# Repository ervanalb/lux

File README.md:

lux
===

Lux is a protocol for the transmission of power and data from a host device to one or more nodes. It is capable of data rates approaching 3 megabits per second and supplying 30 Watts of power over distances of up to 100 feet. It is designed to be easy to implement and uses low-cost cabling and connectors.

Lux was designed as a lighting control protocol, specifically for LED strips. But, it generalizes nicely to any sort of automation on a small to medium scale.

For tech-specs of the protocol, see SPECS.md.

In this repository, you will find:

Library
-------

The lux library is a architecture-independent implementation of the lux in C which you can use to implement your own lux nodes. Simply provide the necessary simple hardware abstraction layer, and you're good to go. The implementation fits in under 8K of program memory and 2K of RAM (1K of which is shared with the application) on a Cortex-M0.

LED strip firmware
------------------

This is a real-world instantiation of the lux protocol to control WS2811 or LPD6803 light strips. It uses a STM32F030 at 48 MHz, which has only 32K of FLASH and 4K of RAM for all of the processing. The code also implements a bootloader for firmware upgrades over lux.

Python
------

There is also a python implementation of a lux master using pyserial.

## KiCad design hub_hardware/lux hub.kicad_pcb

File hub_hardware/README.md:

Lux Hub Hardware
================

History
-------

### Rev 6

#### Errata

- 

##### Bad parts

- U3
- R42
- C3 is short
- Fuse clips
- CON1 holes should be bigger

### Rev 5

- STM32F042
- 6 Lux outputs
    - 48V power, 5V/0V RS-422 data
    - Data lines tied together
    - Rx/Tx enable are indepedent
    - TVS on data lines
    - Per-output PTC fuses (which weren't useful)
- USB for comms & non-48V power
    - Spec'd for 500mA current draw to drive 6 ports
- *Greenwire*: 3v3 reg `U1` pads are incorrect
- *Greenwire*: Inrush limiter changed: `R42 -> C; C1 -> R; R1` unpopulated
- *Greenwire*: RX pin incorrect; shorted to TX LED

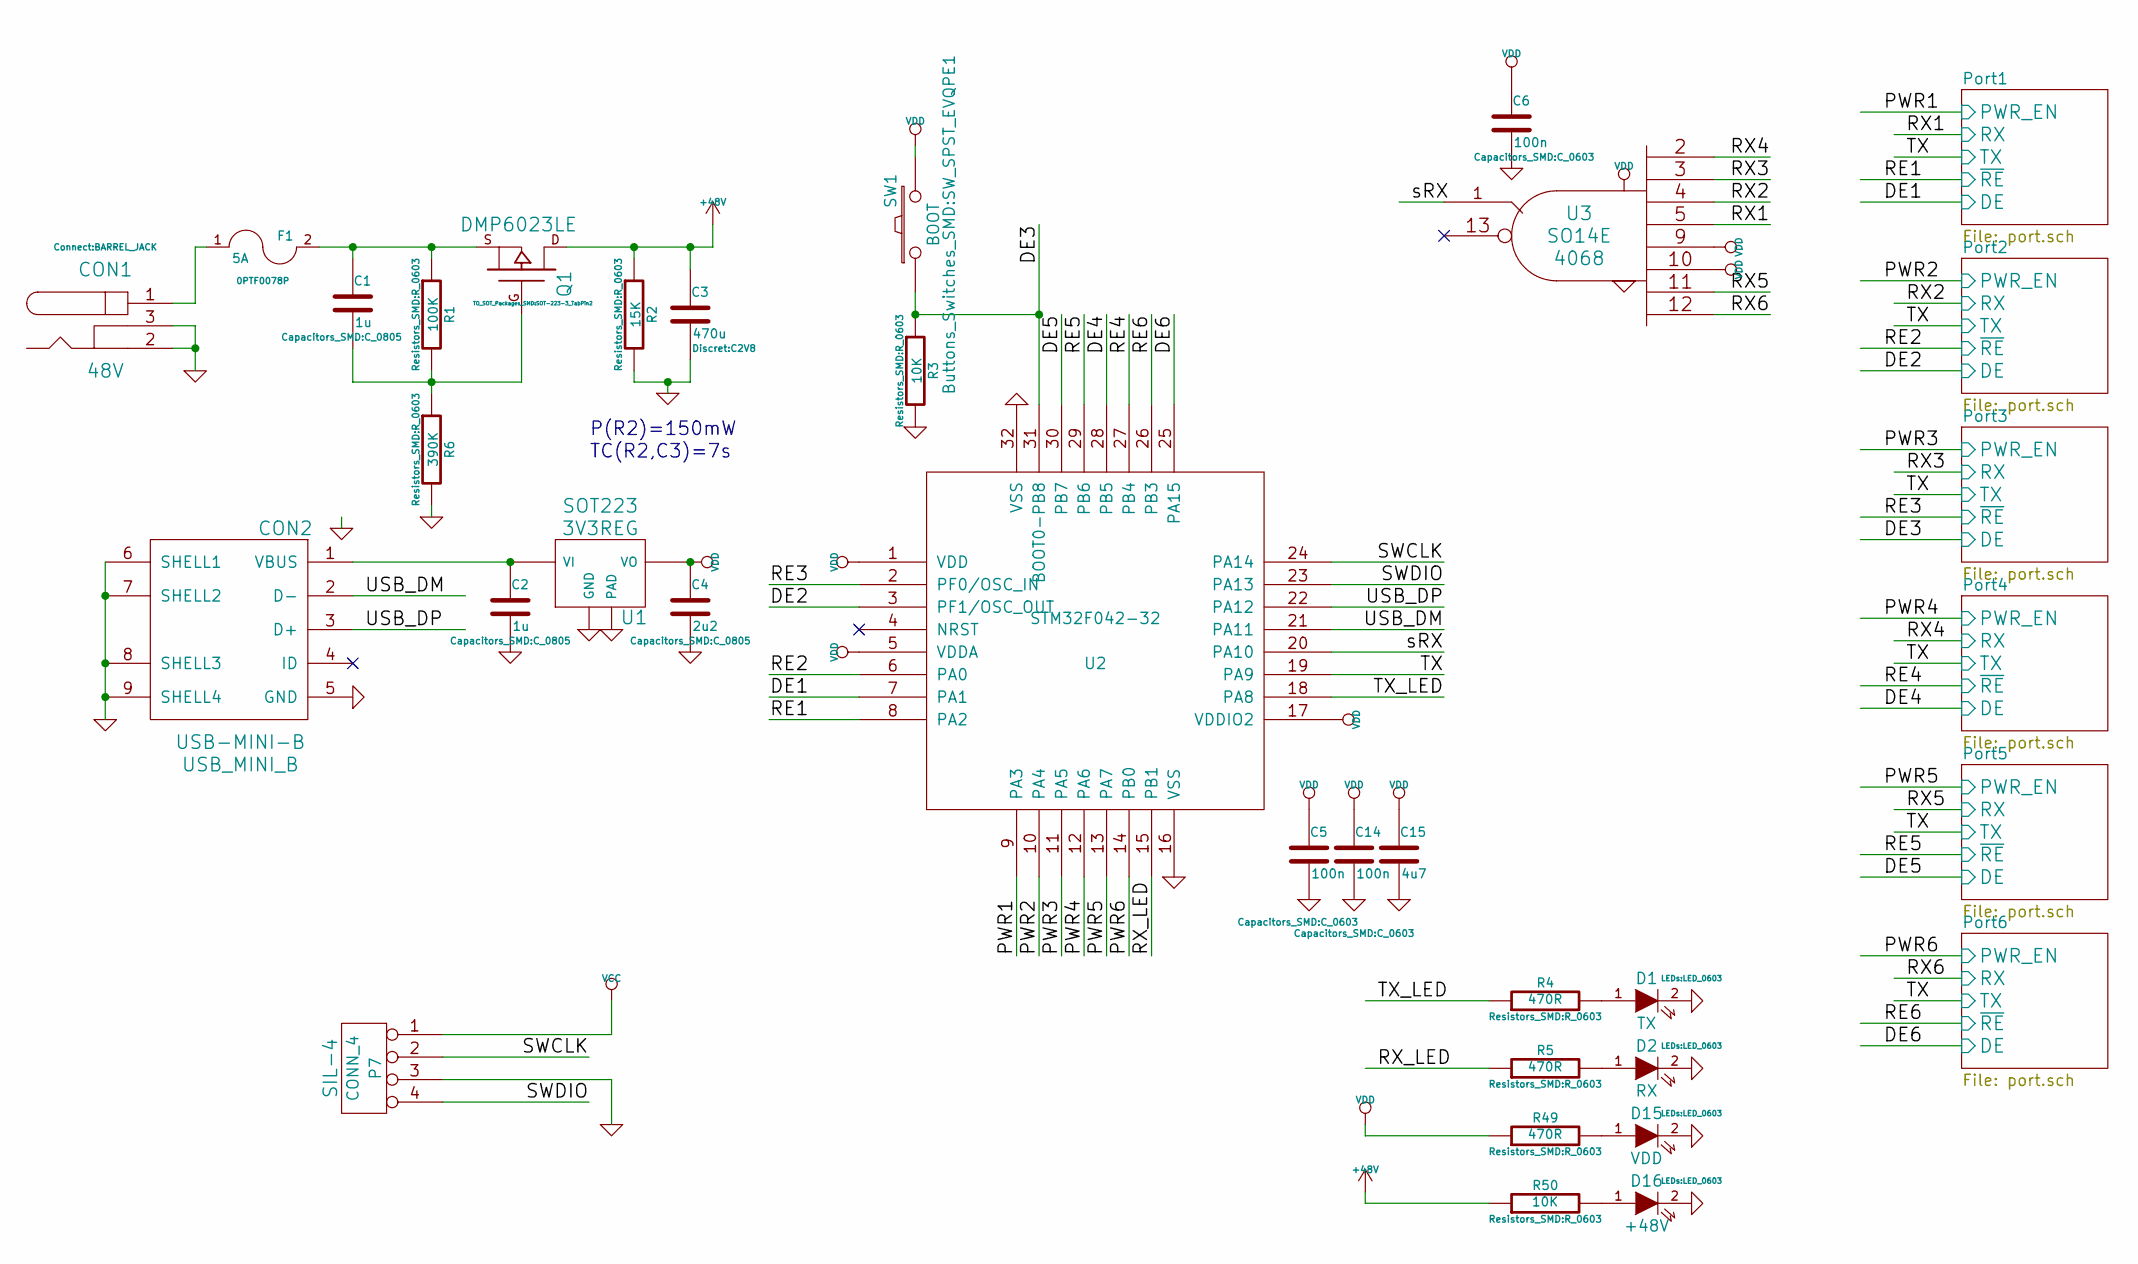
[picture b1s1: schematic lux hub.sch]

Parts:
C1, C2: 1u; C_0805
C3: 470u; C2V8
C4: 2u2; C_0805
C5, C6, C14: 100n; C_0603
C15: 4u7; C_0805
CON1: 48V; BARREL_JACK
CON2: USB-MINI-B; USB_MINI_B
D1: TX; LED_0603
D2: RX; LED_0603
D15: VDD; LED_0603
D16: +48V; LED_0603
F1: 5A; 0PTF0078P
P7: CONN_4; SIL-4
Q1: DMP6023LE; SOT-223-3_TabPin2
R1: 100K; R_0603
R2: 15K; R_0603
R3, R50: 10K; R_0603
R4, R5, R49: 470R; R_0603
R6: 390K; R_0603
SW1: BOOT; SW_SPST_EVQPE1
U1: 3V3REG; SOT223
U2: STM32F042-32; LQFP32
U3: 4068; SO14E

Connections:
+48V: C3.1, Q1.D, R2.1, R50.1; also elsewhere on the board
/DE1: U2.7 (PA1); also elsewhere on the board
/DE2: U2.3 (PF1/OSC_OUT); also elsewhere on the board
/DE3: R3.1, SW1.1, U2.31 (BOOT0-PB8); also elsewhere on the board
/DE4: U2.28 (PB5); also elsewhere on the board
/DE5: U2.30 (PB7); also elsewhere on the board
/DE6: U2.25 (PA15); also elsewhere on the board
/PWR1: U2.9 (PA3); also elsewhere on the board
/PWR2: U2.10 (PA4); also elsewhere on the board
/PWR3: U2.11 (PA5); also elsewhere on the board
/PWR4: U2.12 (PA6); also elsewhere on the board
/PWR5: U2.13 (PA7); also elsewhere on the board
/PWR6: U2.14 (PB0); also elsewhere on the board
/RE1: U2.8 (PA2); also elsewhere on the board
/RE2: U2.6 (PA0); also elsewhere on the board
/RE3: U2.2 (PF0/OSC_IN); also elsewhere on the board
/RE4: U2.27 (PB4); also elsewhere on the board
/RE5: U2.29 (PB6); also elsewhere on the board
/RE6: U2.26 (PB3); also elsewhere on the board
/RX1: U3.5; also elsewhere on the board
/RX2: U3.4; also elsewhere on the board
/RX3: U3.3; also elsewhere on the board
/RX4: U3.2; also elsewhere on the board
/RX5: U3.11; also elsewhere on the board
/RX6: U3.12; also elsewhere on the board
/RX_LED: R5.1, U2.15 (PB1)
/SWCLK: P7.2, U2.24 (PA14)
/SWDIO: P7.4, U2.23 (PA13)
/TX: U2.19 (PA9); also elsewhere on the board
/TX_LED: R4.1, U2.18 (PA8)
/USB_DM: CON2.2 (D-), U2.21 (PA11)
/USB_DP: CON2.3 (D+), U2.22 (PA12)
/sRX: U2.20 (PA10), U3.1
GND: C2.2, C3.2, C4.2, C5.2, C6.2, C14.2, C15.2, CON1.2, CON1.3, CON2.5 (GND), CON2.6 (SHELL1), CON2.7 (SHELL2), CON2.8 (SHELL3), CON2.9 (SHELL4), D1.2 (K), D2.2 (K), D15.2 (K), D16.2 (K), P7.3, R2.2, R3.2, R6.2, U1.2 (GND), U1.4 (PAD), U2.16 (VSS), U2.32 (VSS), U3.7 (GND); also elsewhere on the board
unnamed: C1.1, F1.2, Q1.S, R1.1
unnamed: C1.2, Q1.G, R1.2, R6.1
unnamed: C2.1, CON2.1 (VBUS), U1.1 (VI)
unnamed: CON1.1, F1.1
unnamed: D1.1 (A), R4.2
unnamed: D2.1 (A), R5.2
unnamed: D15.1 (A), R49.2
unnamed: D16.1 (A), R50.2

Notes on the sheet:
P(R2)=150mW
TC(R2,C3)=7s

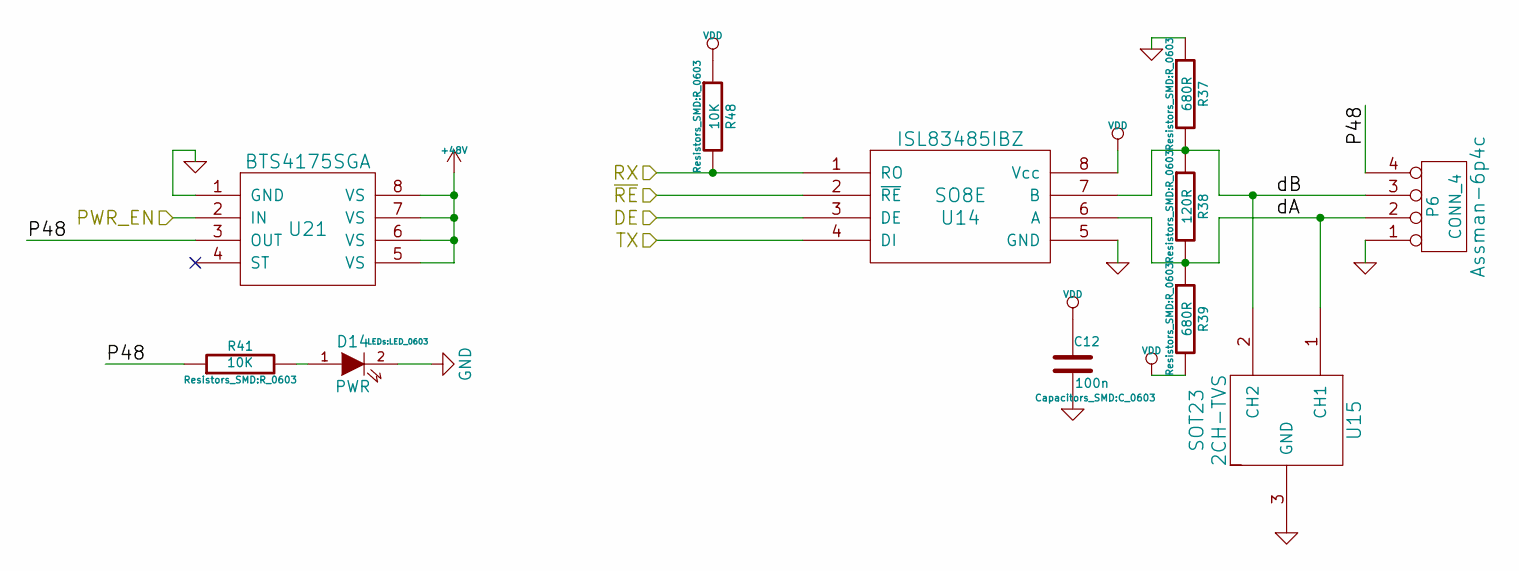
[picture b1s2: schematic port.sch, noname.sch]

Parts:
C7: 100n; C_0603
D4: PWR; LED_0603
P1: CONN_4; Assman-6p4c
R7, R9: 680R; R_0603
R8: 120R; R_0603
R11, R43: 10K; R_0603
U4: ISL83485IBZ; SO8E
U5: 2CH-TVS; SOT23
U16: BTS4175SGA; SOIC-8-N

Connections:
+48V: U16.5 (VS), U16.6 (VS), U16.7 (VS), U16.8 (VS); also elsewhere on the board
/DE1: U4.3 (DE); also elsewhere on the board
/PWR1: U16.2 (IN); also elsewhere on the board
/Port1/P48: P1.4, R11.1, U16.3 (OUT)
/Port1/dA: P1.2, R8.2, R9.1, U4.6 (A), U5.1 (CH1)
/Port1/dB: P1.3, R7.2, R8.1, U4.7 (B), U5.2 (CH2)
/RE1: U4.2 (~RE); also elsewhere on the board
/RX1: R43.2, U4.1 (RO); also elsewhere on the board
/TX: U4.4 (DI); also elsewhere on the board
GND: C7.2, D4.2 (K), P1.1, R7.1, U4.5 (GND), U5.3 (GND), U16.1 (GND); also elsewhere on the board
unnamed: D4.1 (A), R11.2

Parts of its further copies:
C8, C9, C10, C11, C12: 100n; C_0603
D6, D8, D10, D12, D14: PWR; LED_0603
P2, P3, P4, P5, P6: CONN_4; Assman-6p4c
R13, R15, R19, R21, R25, R27, R31, R33, R37, R39: 680R; R_0603
R14, R20, R26, R32, R38: 120R; R_0603
R17, R23, R29, R35, R41, R44, R45, R46, R47, R48: 10K; R_0603
U6, U8, U10, U12, U14: ISL83485IBZ; SO8E
U7, U9, U11, U13, U15: 2CH-TVS; SOT23
U17, U18, U19, U20, U21: BTS4175SGA; SOIC-8-N

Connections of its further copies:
+48V: U17.5 (VS), U17.6 (VS), U17.7 (VS), U17.8 (VS), U18.5 (VS), U18.6 (VS), U18.7 (VS), U18.8 (VS), U19.5 (VS), U19.6 (VS), U19.7 (VS), U19.8 (VS), U20.5 (VS), U20.6 (VS), U20.7 (VS), U20.8 (VS), U21.5 (VS), U21.6 (VS), U21.7 (VS), U21.8 (VS); also elsewhere on the board
/DE2: U6.3 (DE); also elsewhere on the board
/DE3: U8.3 (DE); also elsewhere on the board
/DE4: U10.3 (DE); also elsewhere on the board
/DE5: U12.3 (DE); also elsewhere on the board
/DE6: U14.3 (DE); also elsewhere on the board
/PWR2: U17.2 (IN); also elsewhere on the board
/PWR3: U18.2 (IN); also elsewhere on the board
/PWR4: U19.2 (IN); also elsewhere on the board
/PWR5: U20.2 (IN); also elsewhere on the board
/PWR6: U21.2 (IN); also elsewhere on the board
/Port2/P48: P2.4, R17.1, U17.3 (OUT)
/Port2/dA: P2.2, R14.2, R15.1, U6.6 (A), U7.1 (CH1)
/Port2/dB: P2.3, R13.2, R14.1, U6.7 (B), U7.2 (CH2)
/Port3/P48: P3.4, R23.1, U18.3 (OUT)
/Port3/dA: P3.2, R20.2, R21.1, U8.6 (A), U9.1 (CH1)
/Port3/dB: P3.3, R19.2, R20.1, U8.7 (B), U9.2 (CH2)
/Port4/P48: P4.4, R29.1, U19.3 (OUT)
/Port4/dA: P4.2, R26.2, R27.1, U10.6 (A), U11.1 (CH1)
/Port4/dB: P4.3, R25.2, R26.1, U10.7 (B), U11.2 (CH2)
/Port5/P48: P5.4, R35.1, U20.3 (OUT)
/Port5/dA: P5.2, R32.2, R33.1, U12.6 (A), U13.1 (CH1)
/Port5/dB: P5.3, R31.2, R32.1, U12.7 (B), U13.2 (CH2)
/Port6/P48: P6.4, R41.1, U21.3 (OUT)
/Port6/dA: P6.2, R38.2, R39.1, U14.6 (A), U15.1 (CH1)
/Port6/dB: P6.3, R37.2, R38.1, U14.7 (B), U15.2 (CH2)
/RE2: U6.2 (~RE); also elsewhere on the board
/RE3: U8.2 (~RE); also elsewhere on the board
/RE4: U10.2 (~RE); also elsewhere on the board
/RE5: U12.2 (~RE); also elsewhere on the board
/RE6: U14.2 (~RE); also elsewhere on the board
/RX2: R44.2, U6.1 (RO); also elsewhere on the board
/RX3: R45.2, U8.1 (RO); also elsewhere on the board
/RX4: R46.2, U10.1 (RO); also elsewhere on the board
/RX5: R47.2, U12.1 (RO); also elsewhere on the board
/RX6: R48.2, U14.1 (RO); also elsewhere on the board
/TX: U6.4 (DI), U8.4 (DI), U10.4 (DI), U12.4 (DI), U14.4 (DI); also elsewhere on the board
GND: C8.2, C9.2, C10.2, C11.2, C12.2, D6.2 (K), D8.2 (K), D10.2 (K), D12.2 (K), D14.2 (K), P2.1, P3.1, P4.1, P5.1, P6.1, R13.1, R19.1, R25.1, R31.1, R37.1, U6.5 (GND), U7.3 (GND), U8.5 (GND), U9.3 (GND), U10.5 (GND), U11.3 (GND), U12.5 (GND), U13.3 (GND), U14.5 (GND), U15.3 (GND), U17.1 (GND), U18.1 (GND), U19.1 (GND), U20.1 (GND), U21.1 (GND); also elsewhere on the board
unnamed: D6.1 (A), R17.2
unnamed: D8.1 (A), R23.2
unnamed: D10.1 (A), R29.2
unnamed: D12.1 (A), R35.2
unnamed: D14.1 (A), R41.2

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
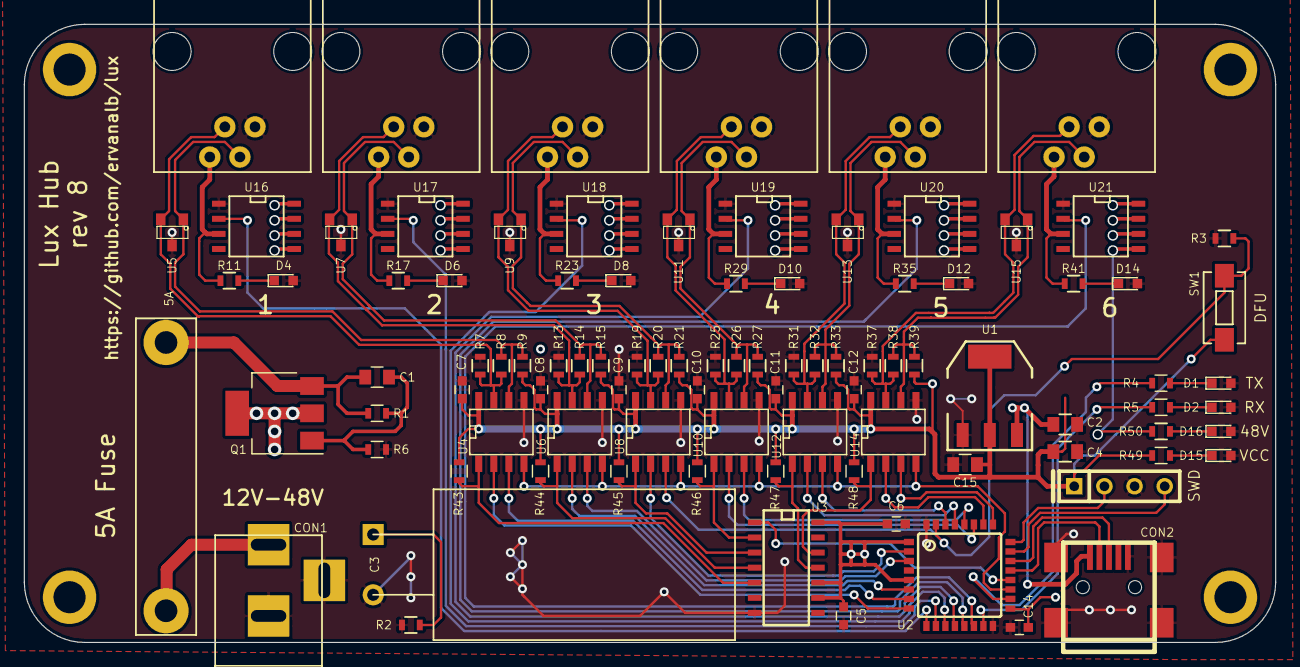
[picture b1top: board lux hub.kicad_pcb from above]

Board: 4 copper layers, 105.4 x 52.1 mm, 95 parts (0 on the bottom side), 67 nets.

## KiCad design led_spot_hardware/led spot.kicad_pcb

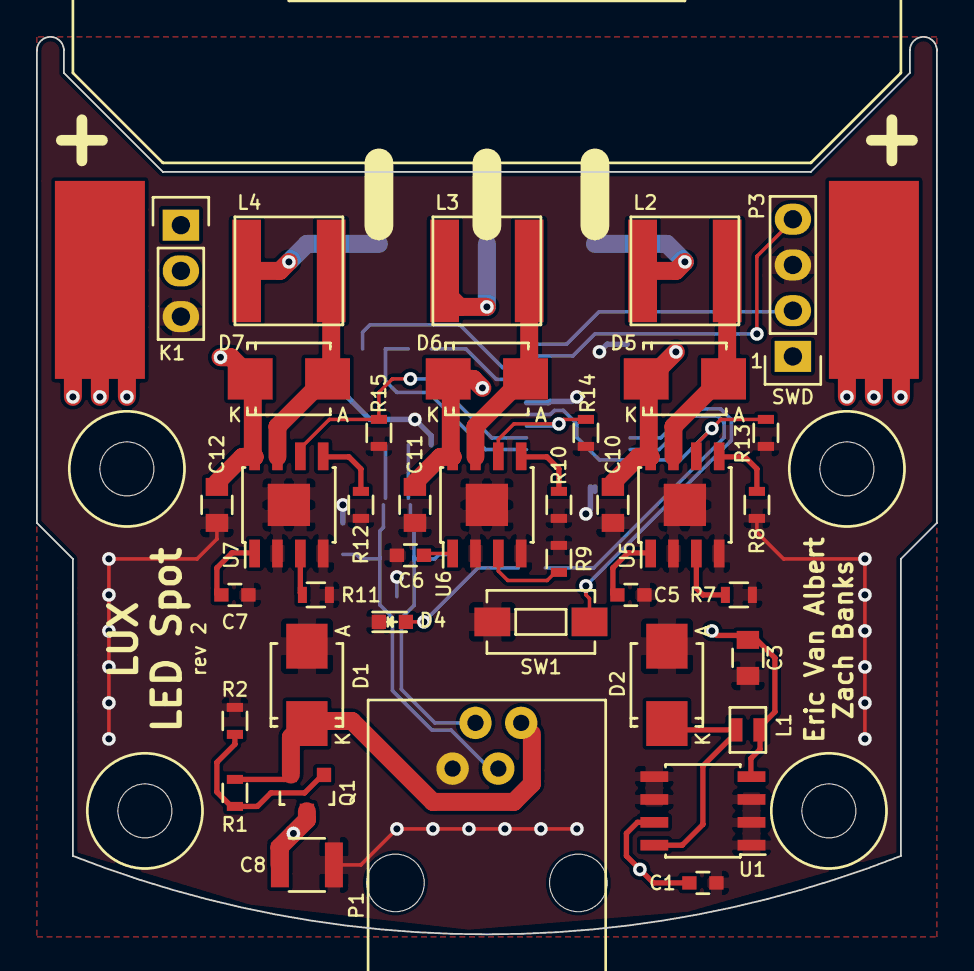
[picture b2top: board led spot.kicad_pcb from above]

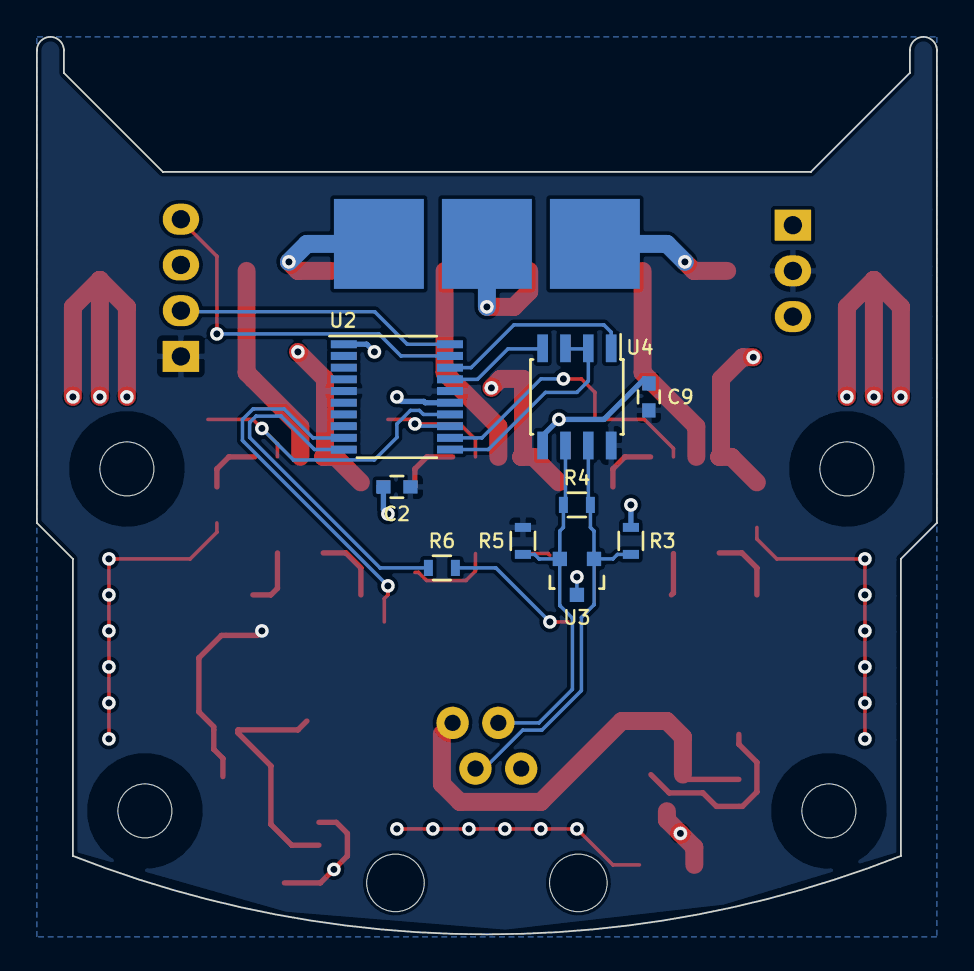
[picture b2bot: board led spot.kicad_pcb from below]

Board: 4 copper layers, 50.0 x 49.9 mm, 53 parts (9 on the bottom side), 31 nets.

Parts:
C1, C2, C9: 100n; C_0603
C3: 4u7; C_0805
C5, C6, C7: 1u; C_0603
C8: 2u2; C_1210
C10, C11, C12: 100n; C_0805
D1: 1SMB58AT3G; SMB_Standard
D2, D5, D6, D7: STPS1H100U; SMB_Standard
D4: USR; LED_0603
HOLE: VAL**; HOLE
HOLE#2, HOLE#3, HOLE#4: VAL**; HOLE
K1: PWR; Pin_Header_Straight_1x03
L1: 22u; VLF-M
L2, L3, L4: 100u; NRS6028T101MMGJ
P1: mod_jack_in; Assman-6p4c
P2: LED; CHINESE-LARGE-LED
P3: SWD; Pin_Header_Straight_1x04
Q1: FDN5618P; SOT-23
R1, R8, R10, R12: 22K; R_0603
R2: 47K; R_0603
R3, R5: 680R; R_0603
R4: 120R; R_0603
R6: 220R; R_0603
R7, R9, R11: 3K3; R_0603
R13, R14, R15: 1K; R_0603
SW1: SW_Push; SW_SPST_EVQPE1
U1: LM2594-HV; SOIC-8_3.9x4.9mm_Pitch1.27mm
U2: STM32F030-20; TSSOP-20_4.4x6.5mm_Pitch0.65mm
U3: 2CH-TVS; SOT-23
U4: ISL83485IBZ; SOIC-8_3.9x4.9mm_Pitch1.27mm
U5, U6, U7: TPS92511; SOIC-8-1EP_3.9x4.9mm_Pitch1.27mm

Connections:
+48V: C1.1, C8.1, C10.1, C11.1, C12.1, D5.1, D6.1, D7.1, K1.1, P2.1, Q1.3, U1.7, U5.8, U6.8, U7.8
/DE: U2.11, U4.2, U4.3
/PWM_B: R15.1, U2.12, U7.6
/PWM_G: R14.1, U2.13, U6.6
/PWM_R: R13.1, U2.14, U5.6
/RX: U2.18, U4.1
/SWCLK: P3.2, U2.20
/SWDIO: P3.4, U2.19
/TX: U2.17, U4.4
/USR_BUTTON: SW1.1, U2.9
/USR_LED: R6.1, U2.10
GND: C1.2, C2.2, C3.2, C5.2, C6.2, C7.2, C8.2, C9.2, C10.2, C11.2, C12.2, D1.2, D2.2, D4.1, K1.3, P1.1, P3.3, R2.2, R3.1, R7.1, R8.1, R9.1, R10.1, R11.1, R12.1, R13.2, R14.2, R15.2, SW1.2, U1.1, U1.2, U1.3, U1.5, U1.6, U2.1, U2.15, U3.3, U4.5, U5.2, U5.4, U5.9, U6.2, U6.4, U6.9, U7.2, U7.4, U7.9
unnamed: C5.1, U5.1
unnamed: C6.1, U6.1
unnamed: C7.1, U7.1
unnamed: D1.1, P1.4, Q1.2, R1.1
unnamed: D2.1, L1.1, U1.8
unnamed: D4.2, R6.2
unnamed: D5.2, L2.1, U5.7
unnamed: D6.2, L3.1, U6.7
unnamed: D7.2, L4.1, U7.7
unnamed: P1.2, R4.2, R5.1, U3.2, U4.6
unnamed: P1.3, R3.2, R4.1, U3.1, U4.7
unnamed: Q1.1, R1.2, R2.1
unnamed: R7.2, U5.3
unnamed: R8.2, U5.5
unnamed: R9.2, U6.3
unnamed: R10.2, U6.5
unnamed: R11.2, U7.3
unnamed: R12.2, U7.5
VCC: C2.1, C3.1, C9.1, K1.2, L1.2, P3.1, R5.2, U1.4, U2.5, U2.16, U4.8

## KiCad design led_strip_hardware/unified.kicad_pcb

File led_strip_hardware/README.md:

LED Strip Hardware
==================

Unified (v5, v6, v7)
------------

v7 Changelog
------------
- Doubled `C1` with `C10` (`+48V` filtering)
- Doubled `C9` with `C11` (`3V3` filtering)
- Added `C12`, 100nF decoupling cap to `U3`
- Improved DFM

v6 Changelog
------------
(Minor revision)
- Added soft-start circuit (`Q1`, `R9`, `R10`) to `+48V`
- Added bias resistors (`R11`, `R12`) to RS-422 lines
- Added transient voltage suppressor (`U5`) to RS-422 lines
- "*Greenwire*": Doubled `C1` (`+48V` filtering)
- "*Greenwire*": Doubled `C9` (`3V3` filtering)
- "*Greenwire*": Added 2x 100nF decoupling caps to `U3`

History
-------

### Rev 5-7

- 2015-2016
- STM32-based
- Comms: RS-422 half-duplex (actually works now)
    - Hub for multiplexing, but not a router
    - Network (UDP) bridge
- Power: 48V + buck
- Rendering: Control-side, full frames sent
- Control: Radiance: https://github.com/zbanks/radiance
    - Visual UI written in C & SDL
    - Effects on a 2D plane, rendered onto strips
    - Tight audio integration & visualization
        - Beat tracking: https://github.com/zbanks/BTrack

### Rev 3-4???

- 2014
- STM32-based
- Comms: RS-422 half-duplex
    - Non-simplex was incredibly unreliable
    - Full router prototyped, never worked
- Power: 48V + buck
- Rendering: Control-side, full frames sent
    - (Bespeckle used intermittently? Unclear)
- Control: Numerous revisions
    - Livecoding python: https://github.com/zbanks/beetle
        - Visual UI with grassroots: https://github.com/zbanks/grassroots
        - #doitlive: https://github.com/zbanks/doitlive
        - Effects projected on a 2D plane and rendered for strips
        - Used audio information (but not well), beats manually sync'd (?)
    - Beat-off: https://github.com/ervanalb/beat-off/tree/python-1d
        - Visual UI
        - 1D LED strips with effects composited
        - Audio info displayed, beats manually sync'd, effects use timing
- Repo: https://github.com/zbanks/aurora

### Rev 2

- Aug 2013
- STM32-based
- Comms: CAN
    - Bastardization of the protocol to get multicast
    - Possibly send-only?
- Power: 48V + buck
- Rendering: Bespeckle, rendering computed on-board
    - https://github.com/zbanks/bespeckle
- Control: Cursedlight, many-keyboards + TUI
    - https://github.com/zbanks/cursedlight
    - Audio manually sync'd
- Repo: https://github.com/ervanalb/canautomation

### Rev 1

- Aug 2012
- CPU: AVR("arduino compatible"!)
- Comms: MIDI
- Power: 12V DC jack
- Rendering: effects computed on board
    - Each MIDI note corresponded to effect + color
- Control: seq24 used for control
    - MIDI clock sync'd from Mixxx

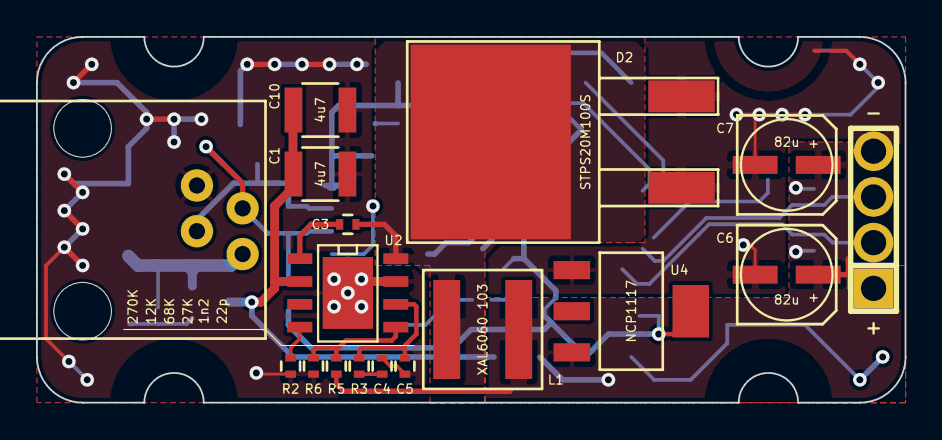
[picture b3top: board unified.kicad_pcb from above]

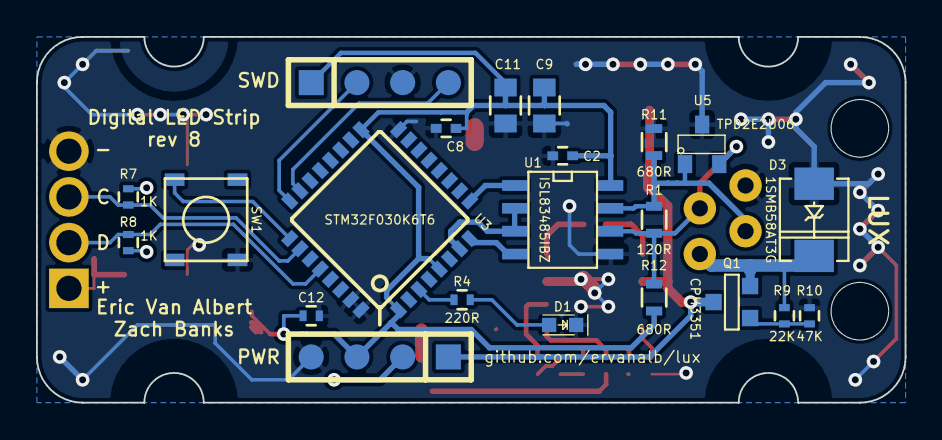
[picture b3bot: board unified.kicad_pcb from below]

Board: 4 copper layers, 48.3 x 20.3 mm, 39 parts (22 on the bottom side), 24 nets.

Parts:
C1, C10: 4u7; C_1210
C2, C8: 100n; C_0402
C3, C12: 100n; R_0402
C4: 1n2; R_0402
C5: 22p; R_0402
C6, C7: 82u; B6
C9, C11: 2u2; C_0805
D1: USR_LED; LED_0603
D2: STPS20M100S; DPAK3
D3: 1SMB58AT3G; DO-214AA(SMB)
L1: XAL6060 103; MSS1210
P1: mod_jack_in; Assman-6p4c
P2: PWR_TST; SIL-4
P3: LED_STRIP; SIL-4
P4: ICSP; SIL-4
Q1: CPH3351; SOT23GDS
R1: 120R; R_0603
R2: 270K; R_0402
R3: 27K; R_0402
R4: 220R; R_0402
R5: 68K; R_0402
R6: 12K; R_0402
R7, R8: 1K; R_0402
R9: 22K; R_0402
R10: 47K; R_0402
R11, R12: 680R; R_0603
SW1: TL3315NF160Q; TACT-SW-SMD
U1: ISL83485IBZ; SO8E
U2: TPS54560; SO8_WITH_EP
U3: STM32F030-32; LQFP32
U4: NCP1117; SOT223
U5: TPD2E2U06; SOT23

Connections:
3V3: C2.1, C8.1, C9.1, C11.1, C12.1, P2.3, P4.1, R12.2, U1.8, U3.1, U3.5, U3.17, U4.2
+48V: C1.1, C10.1, P2.1, Q1.D, U2.2
/CLK: P3.3, R7.2, U3.26
/DAT: P3.2, R8.2, U3.28
/SWCLK: P4.2, U3.24
/SWDAT: P4.4, U3.23
GND: C1.2, C2.2, C4.2, C5.2, C6.2, C7.2, C8.2, C9.2, C10.2, C11.2, C12.2, D1.2, D2.1, D3.1, P1.1, P2.4, P3.4, P4.3, R2.2, R6.2, R10.2, R11.1, SW1.2, U1.5, U2.7, U2.9, U3.16, U3.31, U3.32, U4.1, U5.3
unnamed: C3.1, U2.1
unnamed: C3.2, D2.2, L1.1, U2.8
unnamed: C4.1, R3.2
unnamed: C5.1, R3.1, U2.6
unnamed: D1.1, R4.1
unnamed: D3.2, P1.4, Q1.S, R9.1
unnamed: P1.2, R1.2, R12.1, U1.6, U5.2
unnamed: P1.3, R1.1, R11.2, U1.7, U5.1
unnamed: Q1.G, R9.2, R10.1
unnamed: R2.1, U2.4
unnamed: R4.2, U3.3
unnamed: R5.2, R6.1, U2.5
unnamed: SW1.3, U3.25
unnamed: U1.1, U3.9
unnamed: U1.2, U1.3, U3.7
unnamed: U1.4, U3.8
VPP: C6.1, C7.1, L1.2, P2.2, P3.1, R5.1, R7.1, R8.1, U4.3

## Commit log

2015-02-19 woo first commit
2015-02-19 beginning to implement LUX protocol (rx implemented)
2015-02-19 fixing small bug in COBS implementation
2015-02-23 mostly working lux protocol implementation on the MCU
2015-02-24 cleaning up LUX code quit a bit and adding comments
2015-02-26 communication working fairly well
2015-02-26 speeding up SPI and doing some speed tests
2015-02-27 ws2811 strip bit-bang
2015-02-27 broken; trying to implement DMA interrupts
2015-02-28 changing comment
2015-02-28 first shot at making minimal example for DMA
2015-03-01 minimal working example
2015-03-01 adding infinite loop
2015-03-01 Re-write ser.py to match previous LuxBusDevice abstraction
2015-03-02 first pass at DMA for transferring to LED strips
2015-03-02 changing to ternary operator
2015-03-02 ws2811 working
2015-03-05 adding python directory and perlin noise script
2015-03-05 fixing ws2811 bug and adding some python
2015-03-05 changing parameters of noise demo
2015-03-05 fixing bug in noise.py and improving nosylights
2015-03-11 some changes for the party
2015-03-12 splitting into bootloader
2015-03-22 Fixing makefile so it compiles again
2015-03-22 Adding more commands to LED boards; lux python rx
    LED Boards support:
    - Setting on-board LED state
    - Reading on-board button state
    - Configuring (volatile) unicast/multicast addresses
    - Reading 'id' string ("WS2811 LED Strip")
2015-03-22 adding some bootloader assembly
2015-03-22 Config to flash
2015-03-22 Forgot config.h/c
2015-03-22 attempting drop into bootloader from app
2015-03-22 Writing config ruins the flash; fixed linker
2015-03-22 maybe bootloader will do something now
2015-03-22 Fixed crashes caused by updating flash
2015-03-22 adding reset
2015-03-22 Sleep-dep'd bootloader code
2015-03-22 Bootloader invalidate/reset/read work
2015-03-22 Update README.md
    physical layer
2015-03-23 Update README.md
    DLL and MAC
2015-03-23 Update README.md
    de-facto standards
2015-03-23 adding simple readme
2015-03-23 Bootloader works; python script for uploading
2015-03-23 Refactored app/main.c
2015-03-23 Refactoring python; fixed r/g ws2811
2015-03-23 More clever Makefile: app/config/bl combo + app wo/ config
2015-03-23 Cleaned up bl/main.c, 'spec' in lux_wire.h
2015-03-27 Starting enumeration script
2015-05-30 README
2015-06-02 LED Spotlight
2015-06-04 Better schematic @ervanalb
2015-07-03 Adding schematics/gerbs for router & spotlight
2015-07-07 ST example firmware working
2015-08-27 remove shitty VCP functionality, get closer to raw USB
2015-08-27 SO UNTESTED DIDN'T EVEN COMPILE IT BUT ITS ALL THERE (maybe)
2015-08-29 tx seems to be working well
2015-08-29 move usart irq disable to a more intelligent spot
2015-09-06 add enable / disable of channels
2015-09-08 hub working
2015-09-08 sleep is for the weak
2015-09-08 make strips work
2015-09-14 make lux hub add some space between chunks of data, minor bugfixes all around, everything seems to work
2015-09-15 refactoring lux python protocol
2015-09-15 more tweaks to lux.py
2015-09-15 all of lux seems to work
2015-09-15 flasher doesn't quite work
2015-09-16 everything is broken
2015-09-21 switch back to pyserial
2015-09-22 update spec, port everything to python3
2015-09-23 fix bug in cobs encoder
2015-09-24 lost a return 1
2016-01-22 Lux over UDP?
2016-01-30 Lux over UDP
2016-01-31 fix small bug in lux.py and write lux_udp.py
2016-02-06 Writing docs about new lux
2016-02-06 Lux is now basically USB
2016-02-06 Only one response
2016-02-06 Documenting lux commands under new protocol
2016-02-07 Fix lux.py to work in both python 2.7 & 3.x
2016-02-07 New lux protocol; bl works!
2016-02-07 Lux C lib for unix
2016-02-07 Better lux C lib
2016-02-07 Add ACK to CMD_COMMIT_CONFIG
2016-02-08 More docs
2016-04-23 Adding old lux hub (v4)
2016-04-27 kicad hardware files
2016-05-01 Progress on v7 of led_strip_hardware
2016-05-02 add led spot
2016-05-07 Progress on v7 of led_strip_hardware; some lux utilities
2016-05-07 fix dropped bytes by changing interrupt priorities
2016-05-22 LED hardware rev 7
2016-05-22 LED strip hardware rev 7; added mask gebers & moved via
2016-05-23 LED strip hardware rev 7; ready for prod?
2016-05-23 Cleaned up led strip gerber directory
2016-05-24 More 'final' touches
2016-05-24 Flipped D2; still need to fix silk bottom
2016-05-24 lgtm
2016-05-24 ship it
2016-05-24 add centroid file
2016-05-29 Copper for the hub
2016-06-12 Fix typos
2016-07-02 Update lux protocol specification
2016-07-02 Update liblux API
2016-07-02 Hub gerbers; Reverting changes to lux API;
2016-07-03 udp_bridge.py responds to UDP pings
2016-07-13 LED Strip rev 8
2016-07-14 add BOM for assembly
2016-07-14 fix TVS part no
2016-08-25 lux_test for programming addresses
2017-02-11 X11 -> lux bridge prototype
2017-02-11 Updating .gitignore
2017-02-11 Cleanup liblux to be consistent with radiance; started utils/
2017-02-12 Separate out liblux.so; python cffi wrapper stub
2017-02-18 Break out `lux_(un)frame` from liblux
2018-02-11 Add length support to luxctl
2018-02-23 Rewrite lux firmware
2018-03-18 improvements to LED spot
2018-03-18 finish updating LED spot
2018-03-24 WIP Lux Hub v7
    * Replace PTCs with current-limiting circuit
    * Widen board and add 4x2mm mounting holes
    * TODO: Rearrange some components on the edges
    * TODO: Check silkscreen (esp. LEDs)
2018-03-24 WIP Lux Hub v7; need to re-route 1W 2512 resistors
2018-03-24 WIP Lux Hub v7; proposed re-route
2018-03-26 Lux Hub v7 (done)
2018-03-26 Custom libs for Lux Hub v7
2018-04-01 rev 2 gerbers
2018-04-01 Export hub gebers v7
2018-04-01 Fix inner copper pour
2018-05-12 Add thermal pad SVG for laser cutting
2018-05-16 Lux Hub v8
2018-05-16 Lux Hub v8 - zip w/ gerbers
2018-05-17 Add soft-start circuit to lux hub v8, update gerbers
2018-05-18 Fix ws2811 strip_write function
2018-06-01 fix CMD_COMMIT_CONFIG
2018-06-19 'Fix' led_strip_firmware config.c flash issues, add new commands (read config, detect devices) to luxctl
